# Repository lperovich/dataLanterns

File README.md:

# Open Water Data

The Open Water Data project explores new ways to experience environmental data as a community to increase collective understanding and engagement in important civic conversations. It helps make open source governmental data visible and accessible to community members, advocacy groups, and local governments and turns a critical eye on how open data sets about the environment are shared with the public: Who do these datasets serve and who could they serve? We share all the resources for creating an Open Water Data installation so that other communities can hold similar events and help us all better understand environmental contamination. 

### Chemicals in the Creek
In the Chemicals in the Creek Open Water Data installation, we floated data lanterns onto the Chelsea River in Massachusetts to create a physical representation of Clean Water Act violations by local oil storage facilities. The Clean Water Act (CWA) is a federal law that limits how much and what kinds of harmful chemicals can be put into waterways. From 2013-2017, the seven oil storage facilities in this area violated their CWA permits 76 times. We represent each of these violations with a lantern with a logo from the facility that the violation came from and that is color coded based on the chemical in violation. We hope these lanterns will shed light on the problem of chemicals being released into the creek and begin a community conversation about improving industrial accountability.

[Learn more and see pictures on the Open Water Data Website](http://datalanterns.com/)

### Team

The Chemicals in the Creek installation is led by Laura Perovich (MIT), Sara Wylie (Northeastern Universities Social Science Environmental Health Research Institute), and Roseann Bongiovanni (GreenRoots). The installation was developed with GreenRoots' ECO youth crew and Leilani Mroczkowski from 2017-2018. Contact us if you'd like to create an new Open Water Data installations in your city! Or join our mailing list to find out about future events!

### Materials and Tutorials

All materials are provide here as open and reusable with credit. This includes:
1. Sample R code for gathering Clean Water Act Data from the ECHO website 
2. Sample dataset of NPDES numeric violations from oil storage facilites in Chelsea, MA from 2013-2017
3. Fabrication files: event brochures, event advertisements, year signs, custom seven-color LED board schematics, data lanterns parts lists
4. Detailed supplemental information about our data processes, the Clean Water Act, Environmental Justice, and other related issues. 

[Tutorials for using these resourse and fabricating data lanterns are available on the Open Water Data Website](http://datalanterns.com/#tutorials)

Code, sample data, LED board, and data lanterns parts lists by Laura Perovich.
Event brochures, advertisements, and year signs by Shawn Sullivan with Sara Wylie and Laura Perovich. 
Supplemental information by Laura Perovich, Michael Still, and Sara Wylie. Translation by Gustavo Santiago-Reyes. 

### Thank you

Thanks to everyone who participated in the event and the community meeting, the Chelsea community, the Chelsea Police, Paddle Boston and the Boston University Cyber Law Clinic. Thanks to the undergraduate and graduate students who contributed to this project: Michael Still, Gustavo Santiago-Reyes, Jacqueline Chen, Maggie Zhang, Xavier Mojica, Emily Schachtele, Garance Malivel, and Shawn Sullivan. Thanks to the volunteers that assisted during the event: John Rao, Arushi Sood, Ed Hackett, Sharon Harlan, Olivia Ozkurt, Abbie Keane, Holly Coppes, Hanson Au, Lourdes Vera, Marc Jacobson, Dorian Stump, Angela Stewart, Laura Senier, Grace Poudrier, and Kaline Langley. Thanks to the event photographers and videographers: Rio Asch Phoenix, Will Campbell, Jimmy Day, and David Mussina.

With support from CRESSH, Elements Fellows Program, V. Michael Bove and Object-Based Media, the MIT Media Lab communications team, and RIELS.

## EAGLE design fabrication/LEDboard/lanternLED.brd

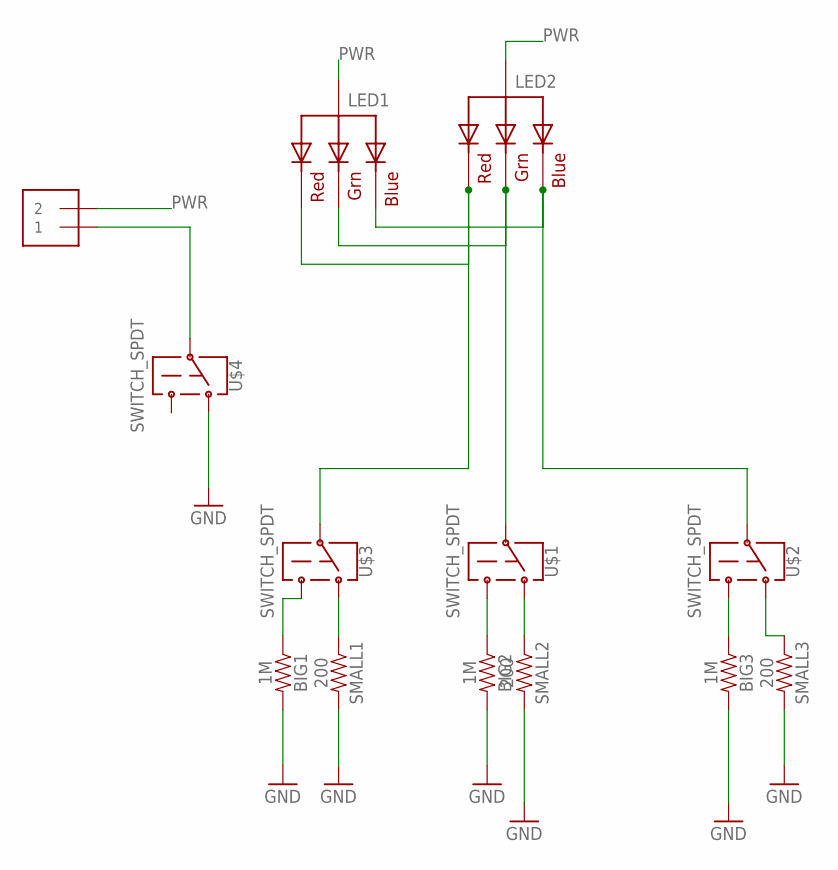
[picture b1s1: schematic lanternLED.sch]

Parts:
BIG1, BIG2, BIG3: 1M; 0603
J1: 1X2BIGGERHOLES; 1X2-4.5MM
LED1, LED2: RGBLED_CA-PIRANHA; PIRANHA5MM
SMALL1, SMALL2, SMALL3: 200; 0603
U$1, U$2, U$3, U$4: SWITCH_SPDT; SWITCH_SPDT_SMD_CLSB12B

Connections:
GND: BIG1.2, BIG2.2, BIG3.2, SMALL1.2, SMALL2.2, SMALL3.2, U$4.SIDER
unnamed: LED1.2 (RED), LED2.2 (RED), U$3.TOP (SINGLE)
unnamed: LED1.3 (GREEN), LED2.3 (GREEN), U$1.TOP (SINGLE)
unnamed: LED1.1 (BLUE), LED2.1 (BLUE), U$2.TOP (SINGLE)
unnamed: BIG1.1, U$3.SIDEL
unnamed: SMALL1.1, U$3.SIDER
unnamed: BIG2.1, U$1.SIDEL
unnamed: SMALL2.1, U$1.SIDER
unnamed: BIG3.1, U$2.SIDEL
unnamed: SMALL3.1, U$2.SIDER
unnamed: J1.1, U$4.TOP (SINGLE)
PWR: J1.2, LED1.4 (VCC), LED2.4 (VCC)

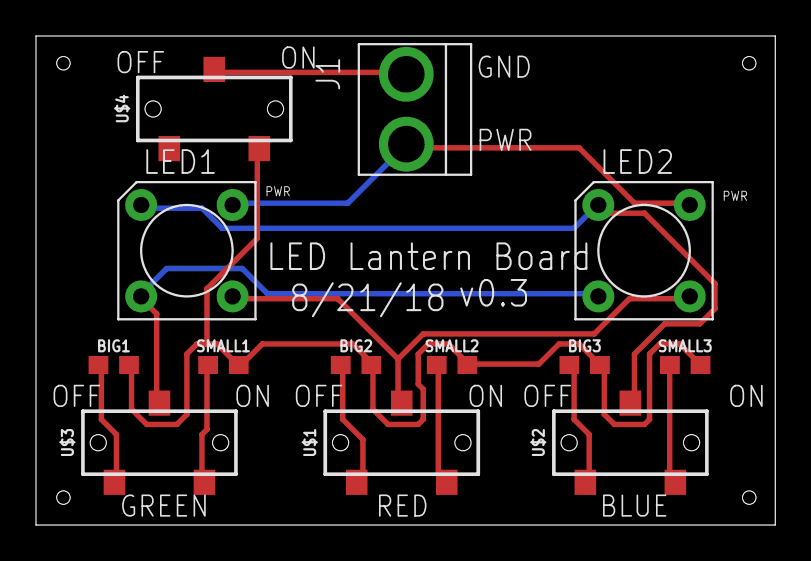
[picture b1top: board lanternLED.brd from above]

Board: 2 copper layers, 41.1 x 27.2 mm, 13 parts (0 on the bottom side), 12 nets.

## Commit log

2018-10-15 try two
2018-10-15 try three
2018-10-15 try four
2018-10-24 added parts list
2018-10-26 added spanish version placeholder
2018-11-07 added data and code, restructured
2018-11-08 supplemental update
2019-02-07 new fabrication materials
2019-02-07 markdown edit
2020-08-19 adding brochures

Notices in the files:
parts and their libraries:
SparkFun-Resistors: Licensing: Creative Commons ShareAlike 4.0 International - https://creativecommons.org/licenses/by-sa/4.0
